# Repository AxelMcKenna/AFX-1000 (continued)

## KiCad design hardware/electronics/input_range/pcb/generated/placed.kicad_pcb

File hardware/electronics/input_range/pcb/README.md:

# E10 input-range PCB candidate

This separate **54 × 36 × 1.6 mm, six-layer candidate** implements the unchanged 28-part E10 schematic. Four Ø2.4 mm M2 holes have all-layer copper/via keepouts with 3.7 mm radius. It does not replace the existing A11 `audio_carrier`, which belongs to the output-stage board. This candidate has no assigned housing datum, component-height allocation or physical fit qualification.

The checked copper has **371 segments, 25 conventional through vias, zero native all-severity/all-track DRC or schematic-parity violations, and zero open connections** in KiCad 10.0.7. Native connectivity closure is an engineering milestone, not a fabrication release or measured preamplifier performance.

## Reproduce

```sh
python3 -m hardware.electronics.input_range.pcb.generate --reviewed --kicad-cli /path/to/kicad-cli
python3 -m hardware.electronics.input_range.pcb.check --kicad-cli /path/to/kicad-cli
python3 -m unittest discover -s tests/tooling -p test_input_range_pcb.py -v
```

`reviewed-copper.json` replays the checked copper only after the complete freshly generated placement matches its recorded hash. `generate --route` instead makes a new conservative routing attempt using the shared E25 routing primitives with board-specific rectangular bounds, clearances, drill exclusions and mounting keepouts. Every generation invalidates the existing verification record. A new attempt must pass the independent checker before use.

The preserved placement-only board is `generated/placed.kicad_pcb`; it has 50 connections before routing. Parent circuit values, all component pins, relay contacts, supply polarity, selected footprint names, faces/poses and mounts are independently checked against a fresh native schematic export and E10's authored circuit contract. The checker reports real native opens rather than trusting the route recipe or search-success flags. The six local feedback/output-to-feedback branches also have independent actual F.Cu graph checks: at least 0.25 mm width and a 12 mm construction limit. Those are layout rules, not a stability or bandwidth guarantee.

## Wiring boundary

J1 is `PROC_IN_L / AGND / PROC_IN_R`; J2 is `PRE_OUT_L / AGND / PRE_OUT_R`. J3 requires protected `P12 / AGND / N12`. J4 retains the parent's local `5V / GAIN_LOW` coil interface. The system harness explicitly connects that local `5V` to **protected `5V_DIG`**, never analog `V5_REG` or an unprotected `_SRC` rail. See the [system interconnect review](../../../wiring/SYSTEM.md).

## Remaining qualification

This exploratory routing uses six layers but **does not implement an uninterrupted analog ground plane**. Quiet returns, coil-current segregation, reference planes, amplifier bypass loops, input guards/capacitance, crosstalk, gain/calibration, stability, noise, distortion and overload/partial-power behavior need design review and measurement. Zero DRC does not establish any of them.

Component values and library footprints are inherited interface candidates. Exact passive/header part numbers, effective capacitance, purchased relay/amplifier package tolerances, copper stackup, soldering/stencil details, fasteners, strain relief and actual lead/body heights remain unqualified. The model deliberately leaves `MPN` empty instead of turning a generic resistor value into a purported purchase part number.

`generated/verification.json` fingerprints the current sources, actual PCB, native records and reused helpers. It keeps physical/audio/assembly and build-ready flags false. No board was ordered, powered, placed into the housing or measured in this work.

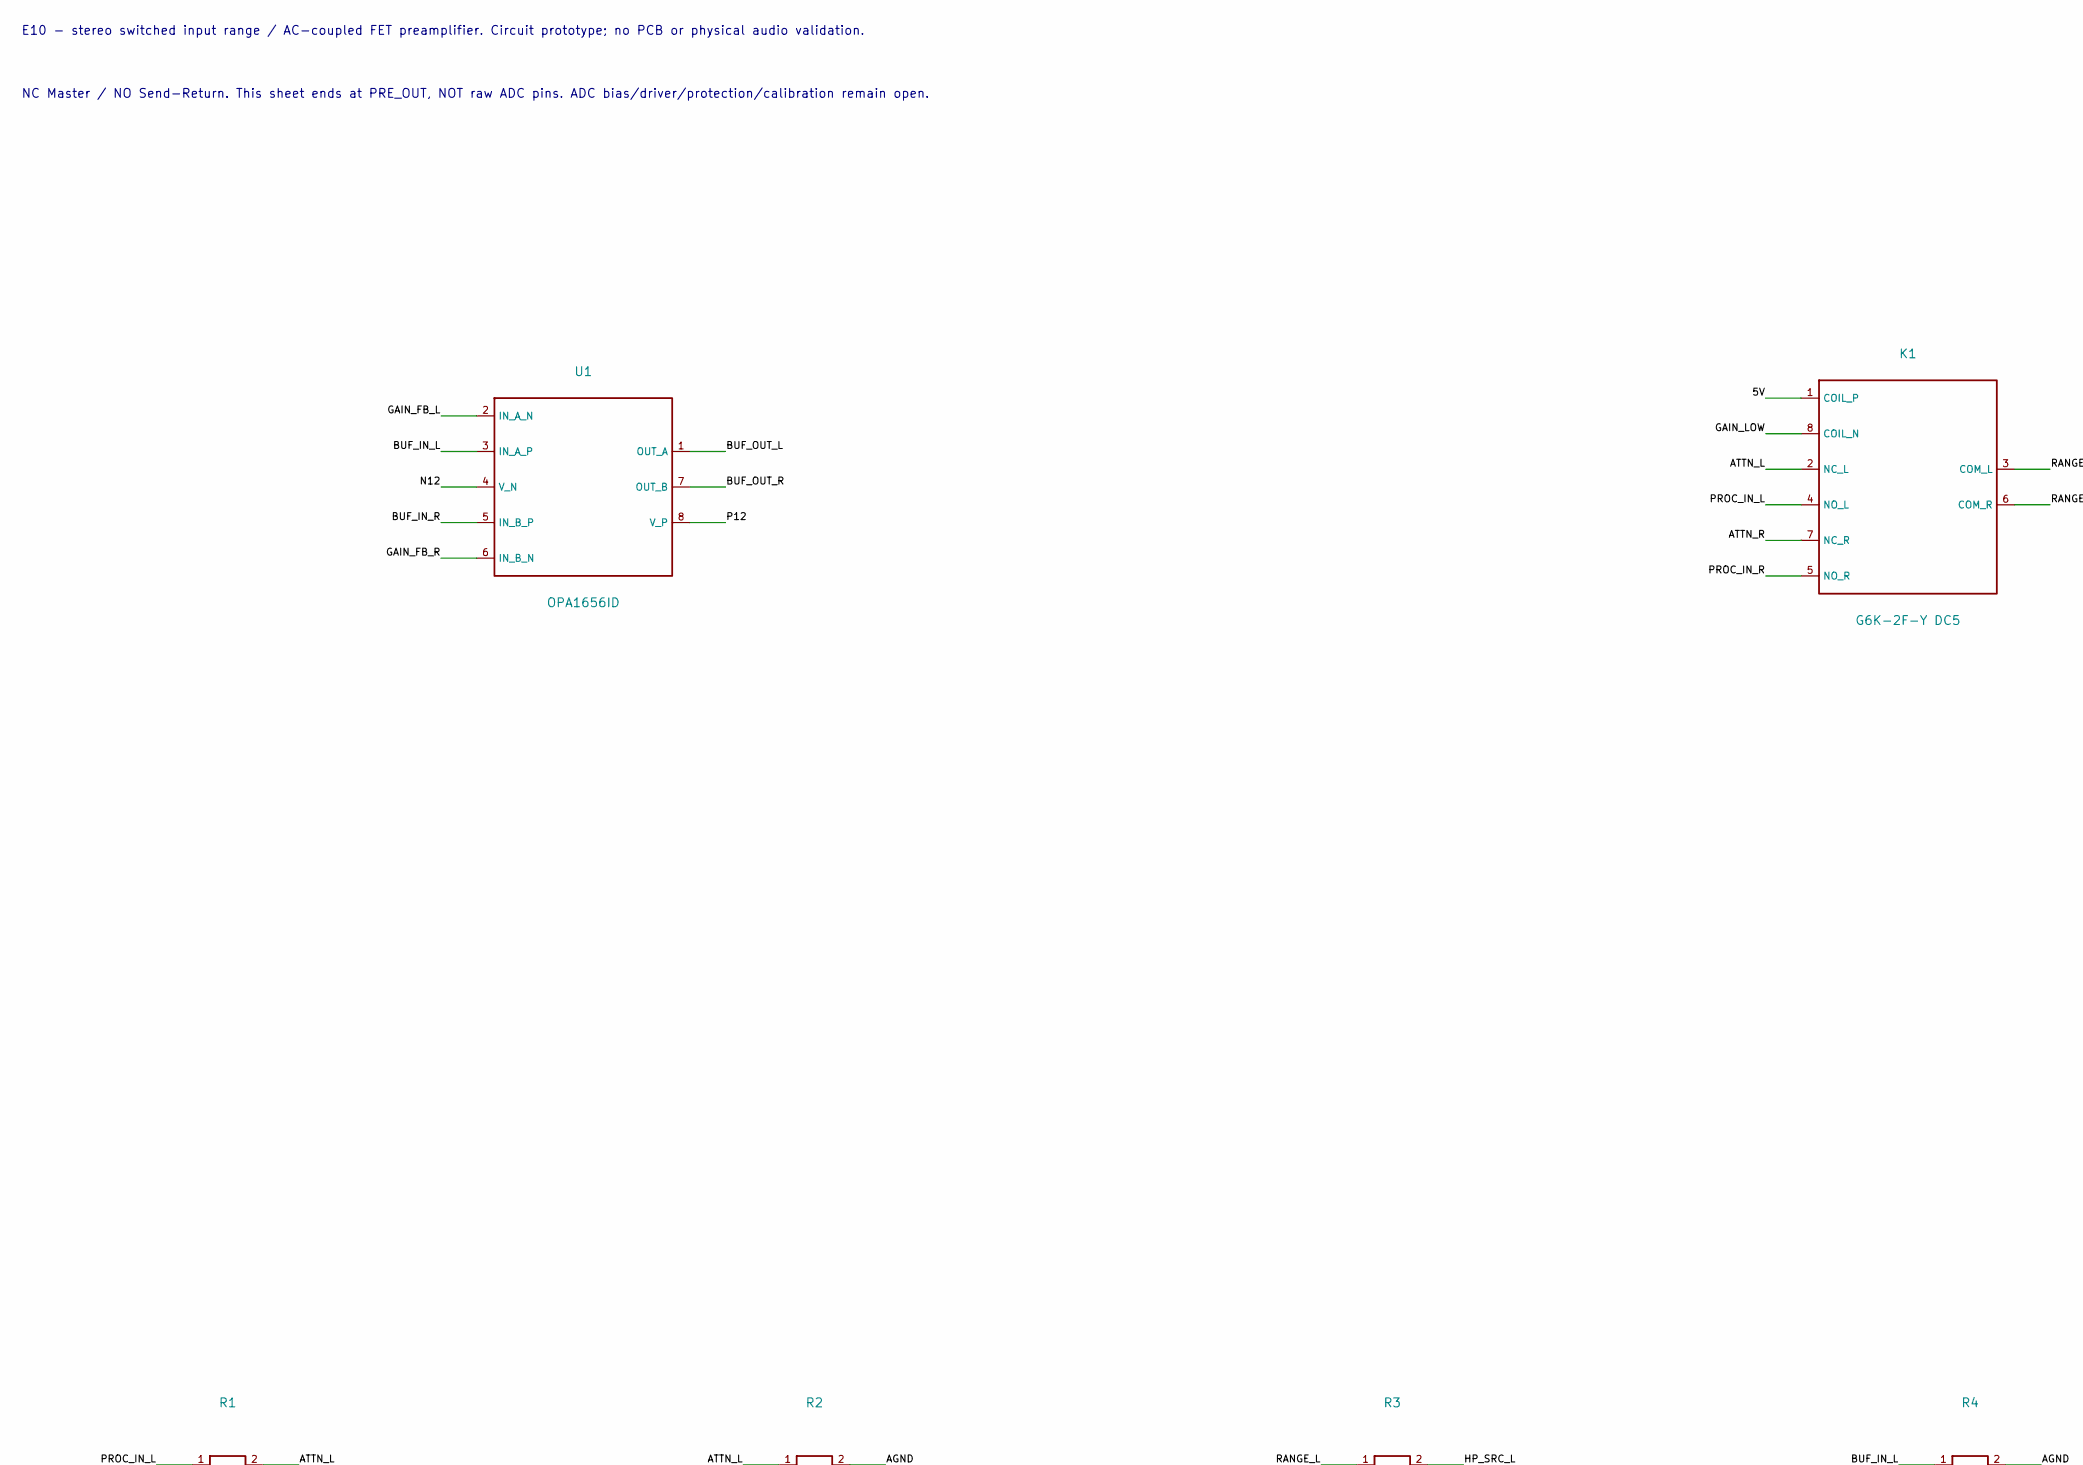
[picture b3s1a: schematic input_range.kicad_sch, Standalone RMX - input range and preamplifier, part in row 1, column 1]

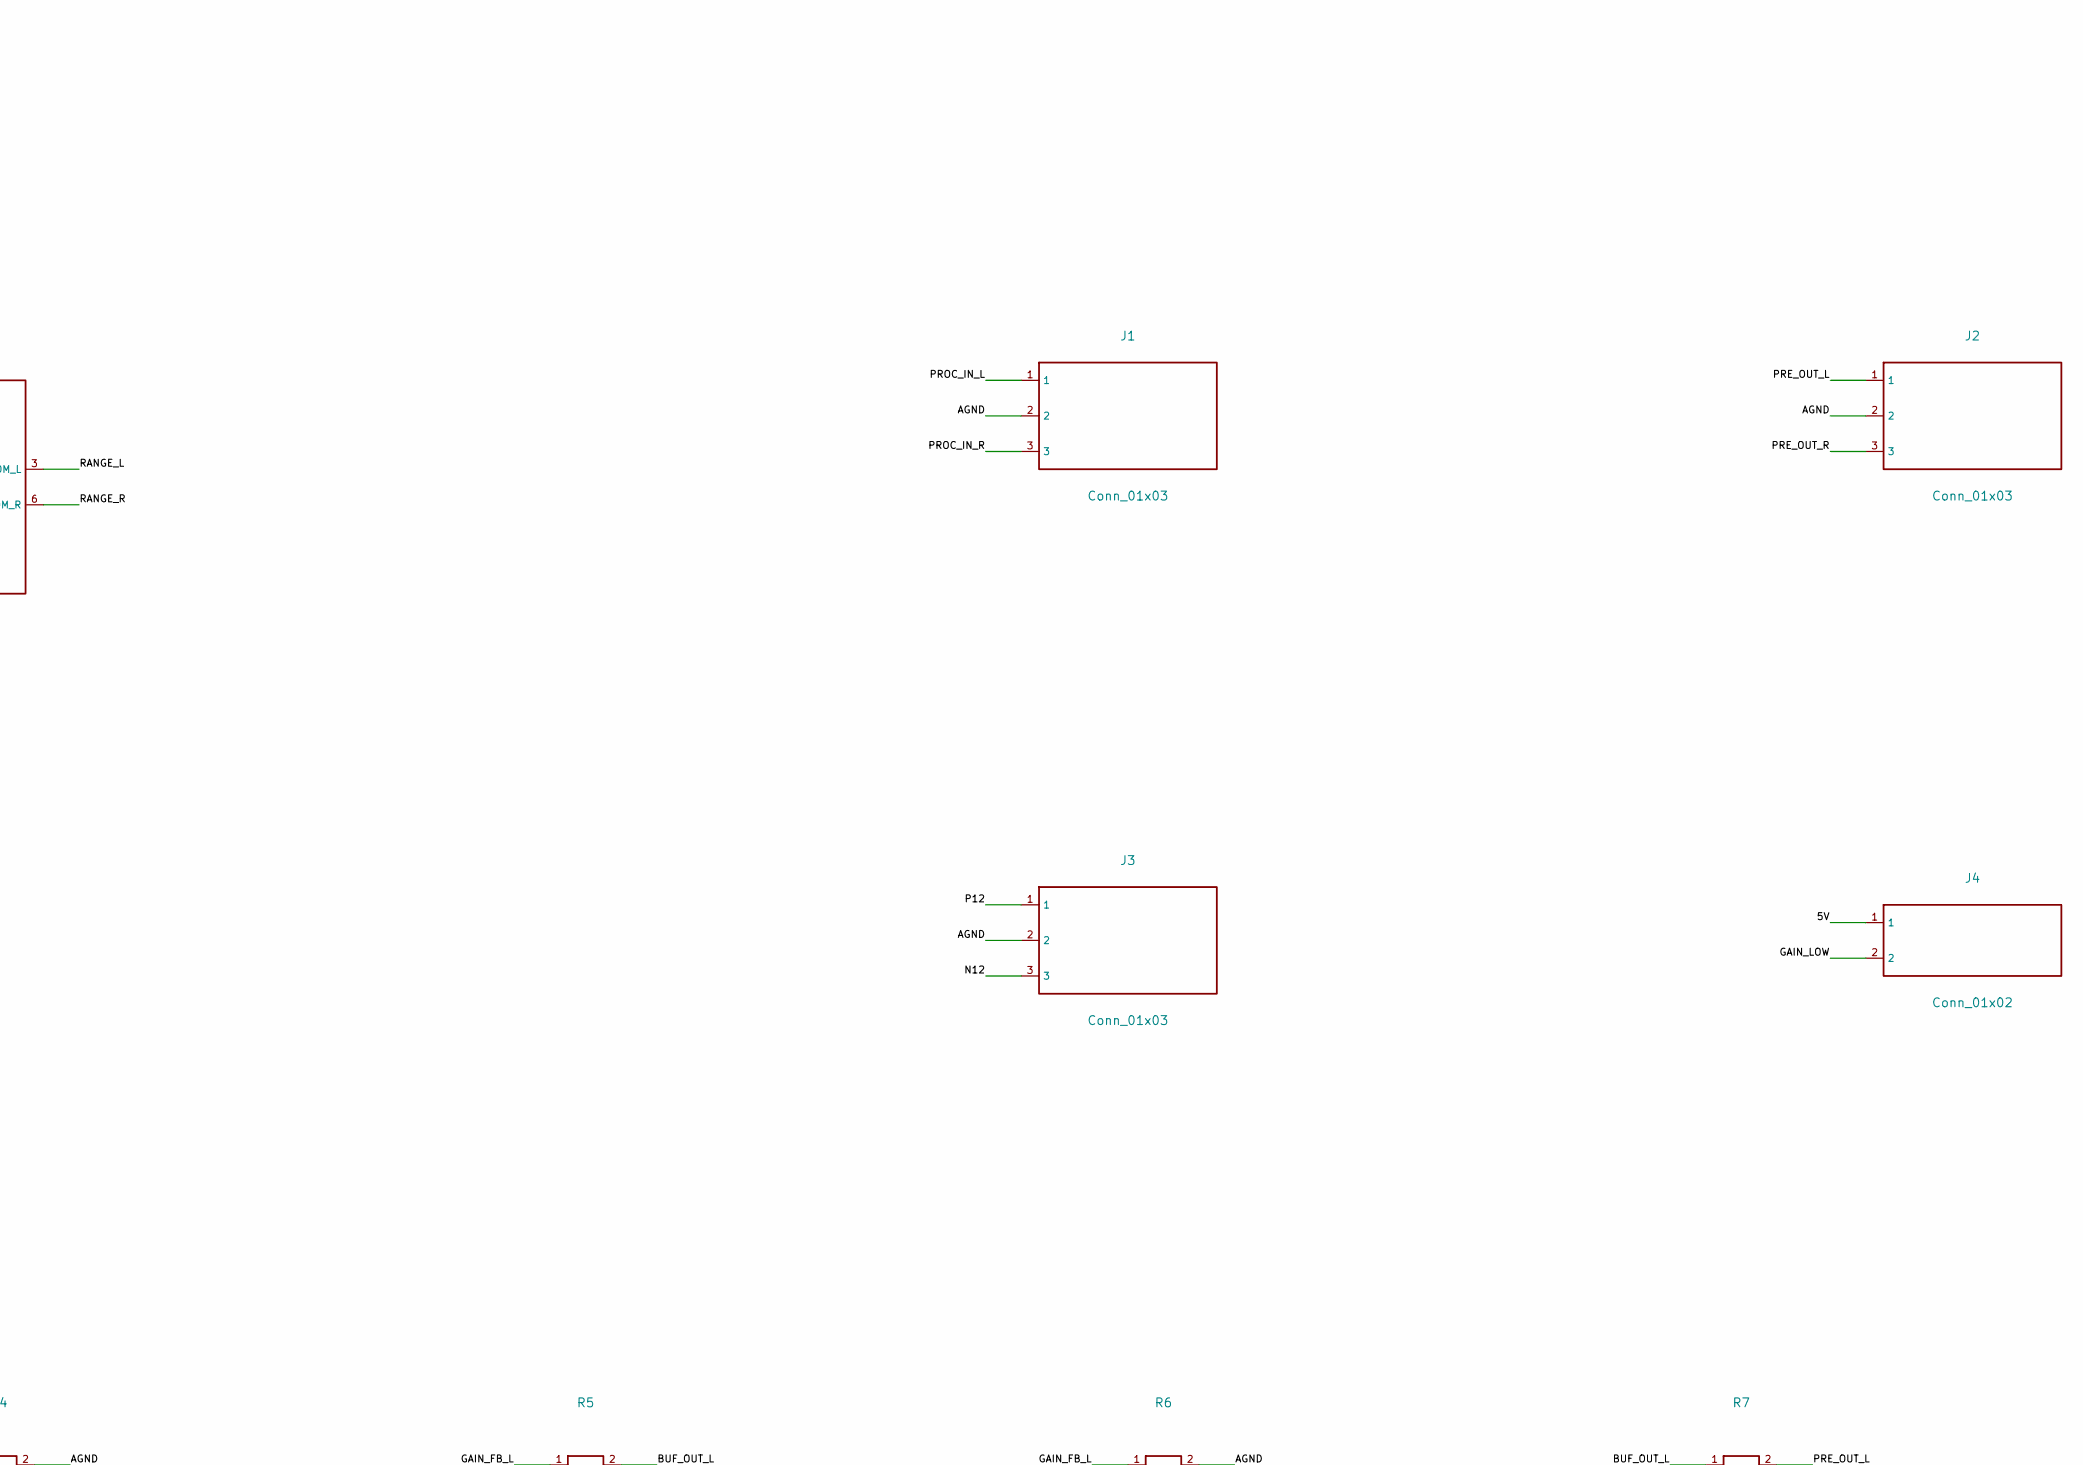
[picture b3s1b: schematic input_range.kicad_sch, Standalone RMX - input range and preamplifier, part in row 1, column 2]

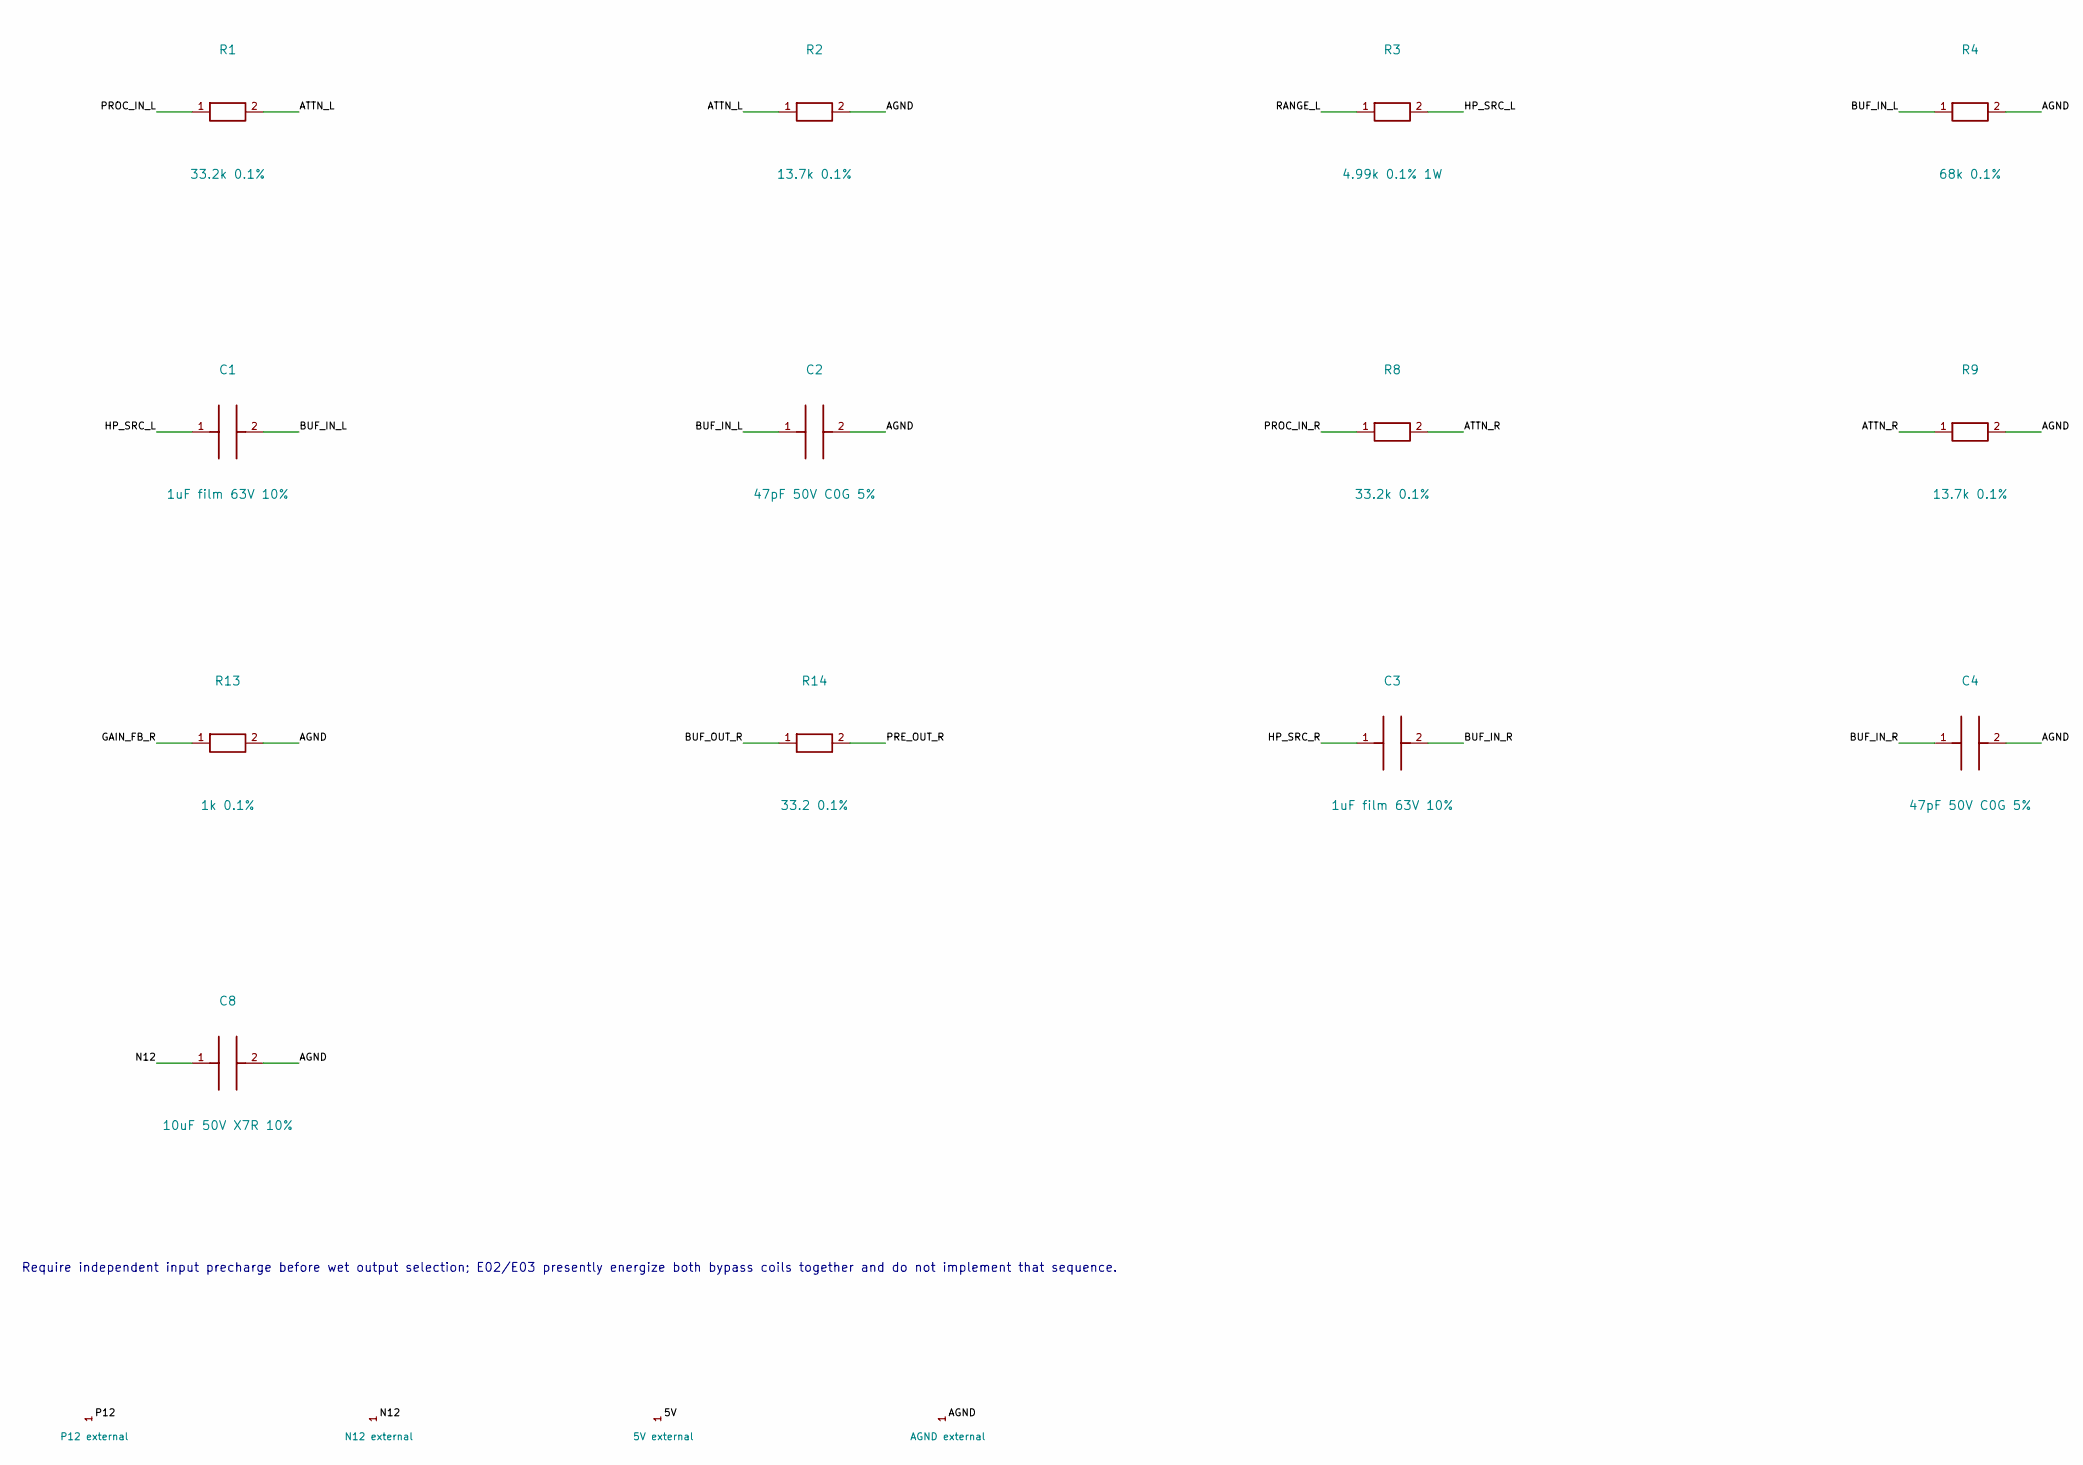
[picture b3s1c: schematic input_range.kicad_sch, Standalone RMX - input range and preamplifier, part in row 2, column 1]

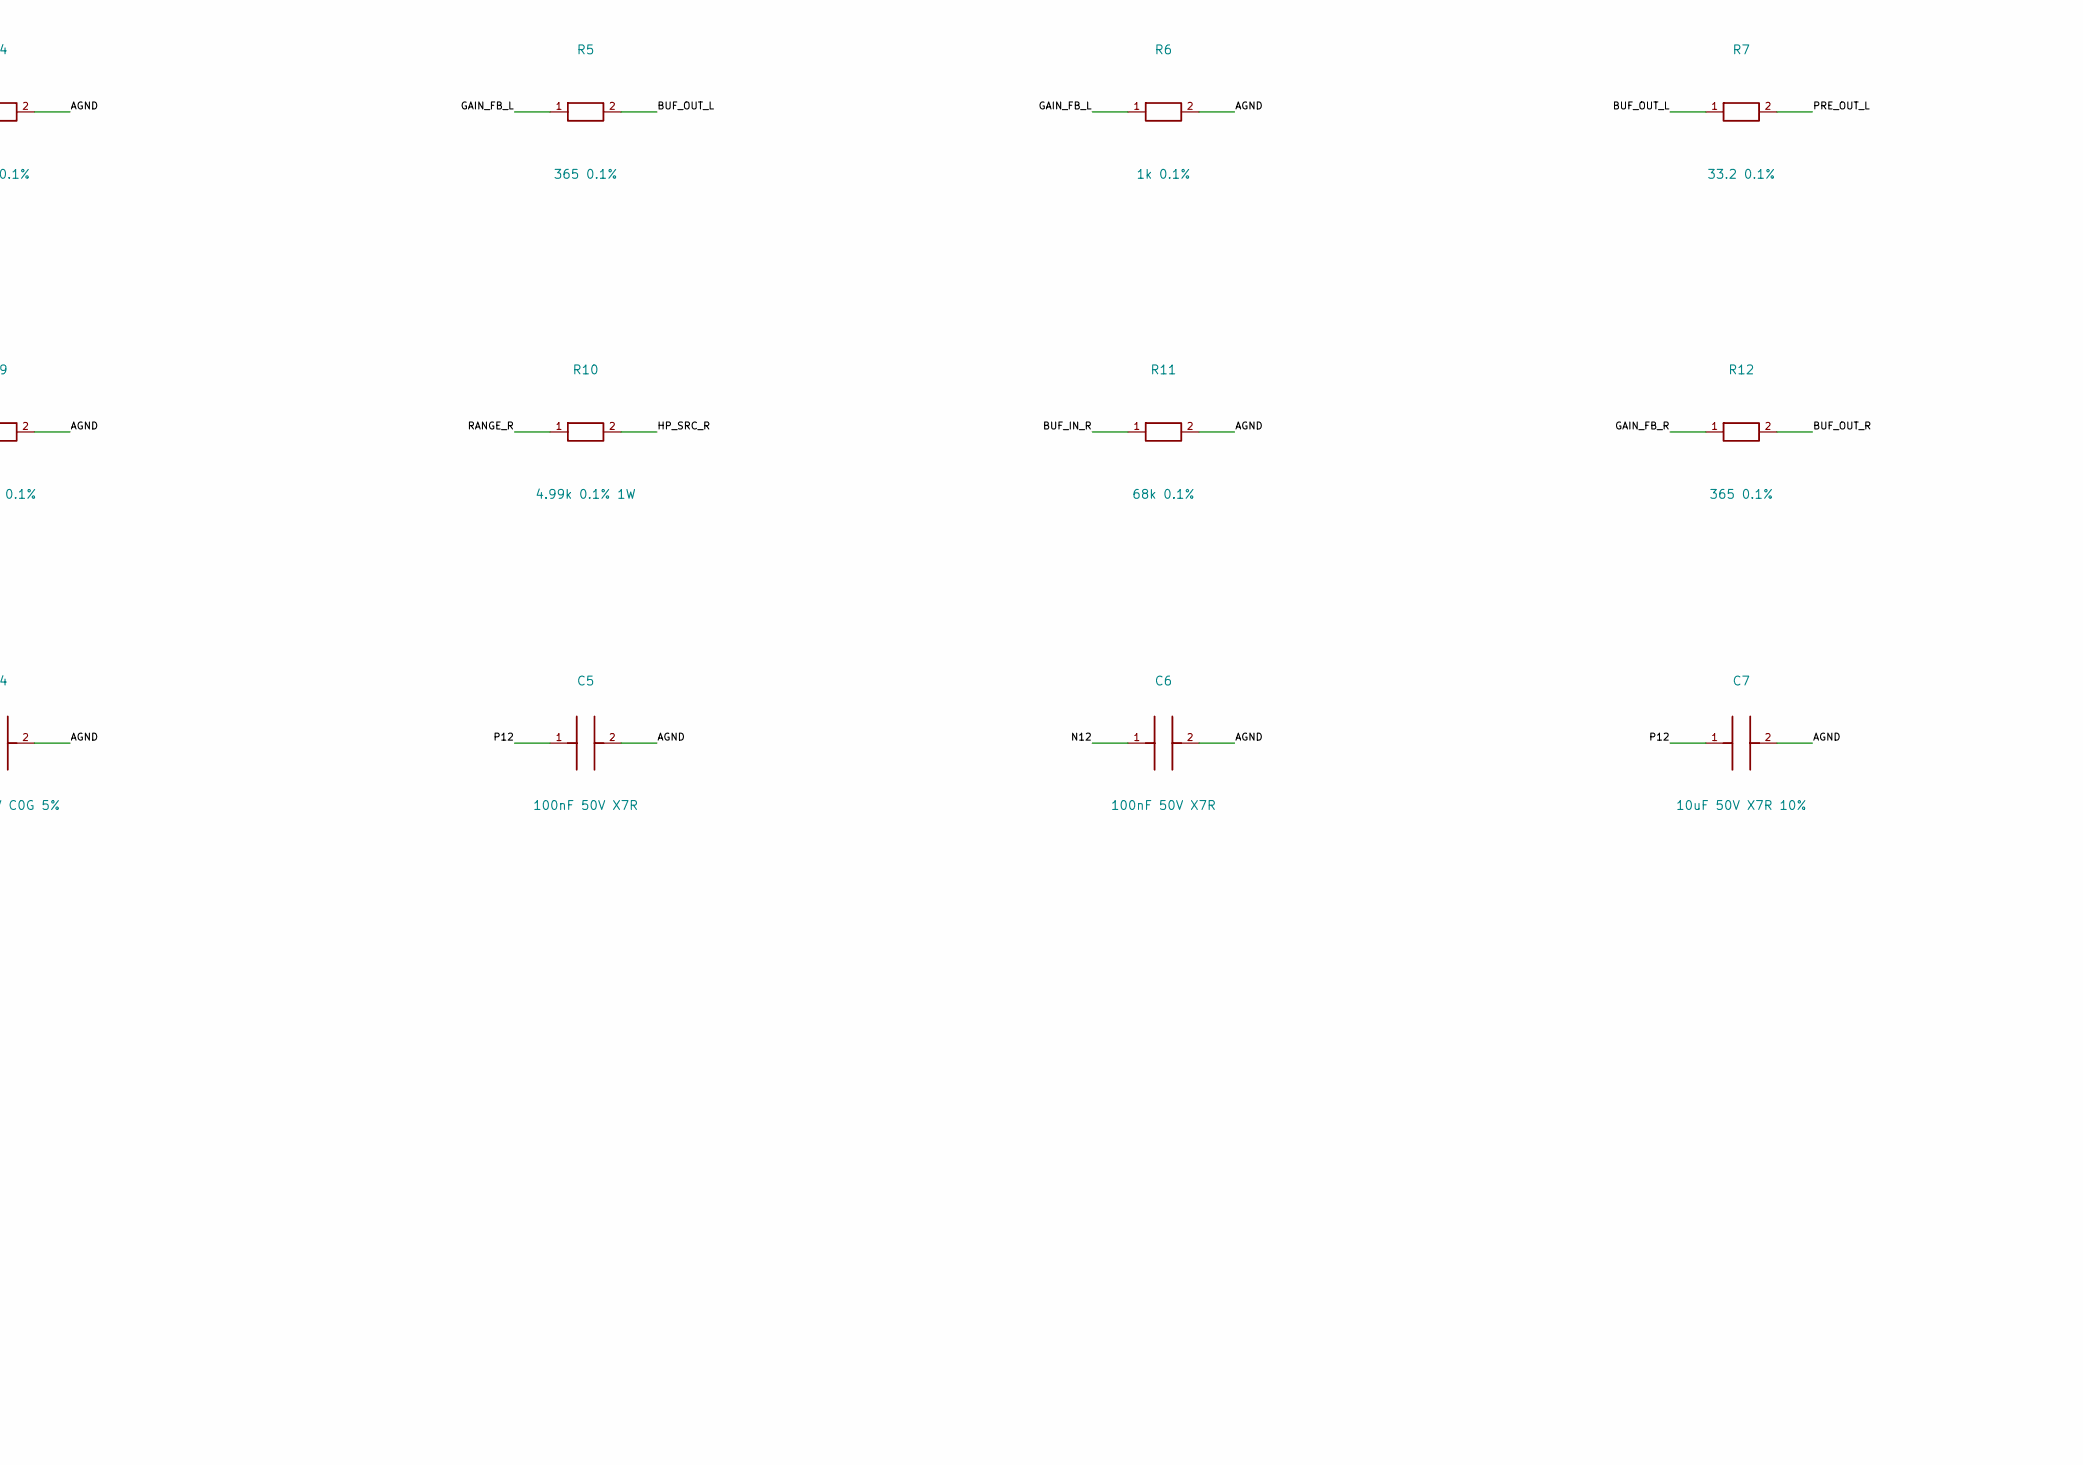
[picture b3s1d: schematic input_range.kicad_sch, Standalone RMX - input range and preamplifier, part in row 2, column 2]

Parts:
C1, C3: 1uF film 63V 10%; C_Rect_L7.2mm_W5.0mm_P5.00mm
C2, C4: 47pF 50V C0G 5%; C_0805_2012Metric
C5, C6: 100nF 50V X7R; C_0805_2012Metric
C7, C8: 10uF 50V X7R 10%; C_1210_3225Metric
J1, J2, J3: Conn_01x03; PinHeader_1x03_P2.54mm_Vertical
J4: Conn_01x02; PinHeader_1x02_P2.54mm_Vertical
K1: G6K-2F-Y DC5; Relay_DPDT_Omron_G6K-2F-Y
R1, R8: 33.2k 0.1%; R_0805_2012Metric
R2, R9: 13.7k 0.1%; R_0805_2012Metric
R3, R10: 4.99k 0.1% 1W; R_2512_6332Metric
R4, R11: 68k 0.1%; R_0805_2012Metric
R5, R12: 365 0.1%; R_0805_2012Metric
R6, R13: 1k 0.1%; R_0805_2012Metric
R7, R14: 33.2 0.1%; R_0805_2012Metric
U1: OPA1656ID; SOIC-8_3.9x4.9mm_P1.27mm

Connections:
/5V: J4.1, K1.1 (COIL_P)
/AGND: C2.2, C4.2, C5.2, C6.2, C7.2, C8.2, J1.2, J2.2, J3.2, R2.2, R4.2, R6.2, R9.2, R11.2, R13.2
/ATTN_L: K1.2 (NC_L), R1.2, R2.1
/ATTN_R: K1.7 (NC_R), R8.2, R9.1
/BUF_IN_L: C1.2, C2.1, R4.1, U1.3 (IN_A_P)
/BUF_IN_R: C3.2, C4.1, R11.1, U1.5 (IN_B_P)
/BUF_OUT_L: R5.2, R7.1, U1.1 (OUT_A)
/BUF_OUT_R: R12.2, R14.1, U1.7 (OUT_B)
/GAIN_FB_L: R5.1, R6.1, U1.2 (IN_A_N)
/GAIN_FB_R: R12.1, R13.1, U1.6 (IN_B_N)
/GAIN_LOW: J4.2, K1.8 (COIL_N)
/HP_SRC_L: C1.1, R3.2
/HP_SRC_R: C3.1, R10.2
/N12: C6.1, C8.1, J3.3, U1.4 (V_N)
/P12: C5.1, C7.1, J3.1, U1.8 (V_P)
/PRE_OUT_L: J2.1, R7.2
/PRE_OUT_R: J2.3, R14.2
/PROC_IN_L: J1.1, K1.4 (NO_L), R1.1
/PROC_IN_R: J1.3, K1.5 (NO_R), R8.1
/RANGE_L: K1.3 (COM_L), R3.1
/RANGE_R: K1.6 (COM_R), R10.1

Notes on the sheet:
E10 - stereo switched input range / AC-coupled FET preamplifier. Circuit prototype; no PCB or physical audio validation.
NC Master / NO Send-Return. This sheet ends at PRE_OUT, NOT raw ADC pins. ADC bias/driver/protection/calibration remain open.
Require independent input precharge before wet output selection; E02/E03 presently energize both bypass coils together and do not implement that sequence.

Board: 6 copper layers, 32 parts (1 on the bottom side), 21 nets, no tracks yet.

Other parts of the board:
H1, H2, H3, H4: M2_CLEARANCE; M2_Clearance

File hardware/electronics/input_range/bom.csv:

Reference,Part_or_value,Footprint_candidate,Datasheet,Design_note
U1,OPA1656ID,Package_SO:SOIC-8_3.9x4.9mm_P1.27mm,https://www.ti.com/lit/ds/symlink/opa1656.pdf,"Dual FET input preamplifier, nominal gain1.365. +/-12V only. Gain resistor remains subject to full ADC-scale calibration."
K1,G6K-2F-Y DC5,Relay_SMD:Relay_DPDT_Omron_G6K-2F-Y,https://omronfs.omron.com/en_US/ecb/products/pdf/en-g6k.pdf,"Released NC=Master attenuated; energized NO=Send/Return. Second gain coil on E02 driver, independent of wet/dry selection."
J1,Conn_01x03,Connector_PinHeader_2.54mm:PinHeader_1x03_P2.54mm_Vertical,,E03 processing input J3.1..3. Its input-isolation coil currently shares wet/dry enable; independent precharge sequencing is not implemented.
J2,Conn_01x03,Connector_PinHeader_2.54mm:PinHeader_1x03_P2.54mm_Vertical,,"Single-ended preamplifier output to future ADC driver, NOT E09 raw ADC input. Analysis assumes load>=100kOhm; scale/bias/protection unresolved."
J3,Conn_01x03,Connector_PinHeader_2.54mm:PinHeader_1x03_P2.54mm_Vertical,,Qualified regulated +/-12V; rail generation/monitoring external.
J4,Conn_01x02,Connector_PinHeader_2.54mm:PinHeader_1x02_P2.54mm_Vertical,,Same pair/order as E02 J5 and E05 J3; second of two proposed gain coils.
R1,33.2k 0.1%,Resistor_SMD:R_0805_2012Metric,,Master divider upper; remains connected in both ranges.
R2,13.7k 0.1%,Resistor_SMD:R_0805_2012Metric,,Master divider lower; includes the actual following bias network load.
R3,4.99k 0.1% 1W,Resistor_SMD:R_2512_6332Metric,,Limits a hypothetical48V input/capacitor step to<10mA; exact resistor/pulse/temperature qualification open.
R4,68k 0.1%,Resistor_SMD:R_0805_2012Metric,,FET input DC return; hot bias/leakage allocation and input precharge interval required.
R5,365 0.1%,Resistor_SMD:R_0805_2012Metric,,Nominal gain resistor. Final value requires complete ADC input-scale measurements.
R6,1k 0.1%,Resistor_SMD:R_0805_2012Metric,,Noninverting gain ground leg.
R7,33.2 0.1%,Resistor_SMD:R_0805_2012Metric,,Output isolation; future ADC driver must present>=100kOhm in-band.
C1,1uF film 63V 10%,Capacitor_THT:C_Rect_L7.2mm_W5.0mm_P5.00mm,https://wima.de/wp-content/uploads/media/e_WIMA_MKS_2.pdf,"WIMA MKS2C041001F00KSSD candidate: nominal7.2x5x10mm body,5mm pitch. Nonpolar; leakage/temperature/fit not measured."
C2,47pF 50V C0G 5%,Capacitor_SMD:C_0805_2012Metric,,RF shunt; not a rated surge/ESD suppressor.
R8,33.2k 0.1%,Resistor_SMD:R_0805_2012Metric,,Master divider upper; remains connected in both ranges.
R9,13.7k 0.1%,Resistor_SMD:R_0805_2012Metric,,Master divider lower; includes the actual following bias network load.
R10,4.99k 0.1% 1W,Resistor_SMD:R_2512_6332Metric,,Limits a hypothetical48V input/capacitor step to<10mA; exact resistor/pulse/temperature qualification open.
R11,68k 0.1%,Resistor_SMD:R_0805_2012Metric,,FET input DC return; hot bias/leakage allocation and input precharge interval required.
R12,365 0.1%,Resistor_SMD:R_0805_2012Metric,,Nominal gain resistor. Final value requires complete ADC input-scale measurements.
R13,1k 0.1%,Resistor_SMD:R_0805_2012Metric,,Noninverting gain ground leg.
R14,33.2 0.1%,Resistor_SMD:R_0805_2012Metric,,Output isolation; future ADC driver must present>=100kOhm in-band.
C3,1uF film 63V 10%,Capacitor_THT:C_Rect_L7.2mm_W5.0mm_P5.00mm,https://wima.de/wp-content/uploads/media/e_WIMA_MKS_2.pdf,"WIMA MKS2C041001F00KSSD candidate: nominal7.2x5x10mm body,5mm pitch. Nonpolar; leakage/temperature/fit not measured."
C4,47pF 50V C0G 5%,Capacitor_SMD:C_0805_2012Metric,,RF shunt; not a rated surge/ESD suppressor.
C5,100nF 50V X7R,Capacitor_SMD:C_0805_2012Metric,,Local U1 supply bypass
C6,100nF 50V X7R,Capacitor_SMD:C_0805_2012Metric,,Local U1 supply bypass
C7,10uF 50V X7R 10%,Capacitor_SMD:C_1210_3225Metric,,"Require effective>=4.7uF on +/-12V; exact MPN, bias/temperature/ESR unqualified."
C8,10uF 50V X7R 10%,Capacitor_SMD:C_1210_3225Metric,,"Require effective>=4.7uF on +/-12V; exact MPN, bias/temperature/ESR unqualified."

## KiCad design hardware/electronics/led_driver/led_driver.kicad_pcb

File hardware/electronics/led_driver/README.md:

# E20 LED and BPM driver

E20 implements the 96-output feedback interface used by the standalone firmware:
four TLC5947DAPR constant-current drivers, a 3.3-to-5 V translator, and independent
3.3 V/5 V supervisors. It covers the driver core. The front-panel emitter boards,
display wiring, ring optics and production harnesses are unfinished.

The independent [verification record](generated/verification.json), when present,
states whether the native PCB is placed or routed. An explicitly requested
`--placed-only` result permits open connections and is not a routing approval.
The normal verifier requires zero native ERC, DRC, schematic-parity and open
connections, and a saved ground-plane fill. No physical qualification is claimed.

## Power and startup

The four TLC5947s use `5V_DIG`. Their 16.5 kΩ IREF resistors set approximately
2.98 mA per output by TI's nominal formula. The drivers' guaranteed accuracy and
ICC test conditions are at other reference currents; 2.98 mA is not an established
maximum. The provisional engineering allocation is 4 mA per sink, 90 mA ICC per
driver and 20 mA miscellaneous load: **764 mA total**, including the emitters.
That allocation requires physical verification at the selected IREF value.

U5 is an SN74LVC8T245PWR. VCCA and its input controls use `V3V3_IO` from the
processor; VCCB uses `5V_DIG`. DIR is held high. Four channels translate the
firmware's MOSI, clock, latch and BLANK signals. Four unused A inputs are grounded,
with the corresponding B outputs unconnected. Each active output has a 33 Ω
series resistor. Receiving BLANK is pulled high to keep the drivers off while
the translator is disabled; the other three receiving signals have pulldowns.

TPS3808G33/G50 supervisors monitor both domains. Their settled PG outputs drive
two series NMOS switches: both must be high to pull translator `/OE` low. Missing
or unsettled power leaves `/OE` pulled high. The independent checker follows the
actual MOSFET body-diode directions in eight ideal PG/BLANK combinations. This
does not establish real brownout, back-power or restore-frame behavior.

Firmware holds BLANK high at startup and on SPI failure, shifts each new frame
into the separate shift registers, and explicitly provides 1 µs guards
before/after the latch pulse and before clearing BLANK. Host wire tests model
four cascaded 288-bit shift registers and walk all 1,152 PWM bits. Physical SPI
edge timing, cable integrity and recovery still need measurement.

## Connections

| Connector | Assignment |
| --- | --- |
| J1, 2×4, 1.27 mm | 1 AGND; 2 5V_DIG; 3 V3V3_IO; 4 LED_MOSI; 5 LED_SCK; 6 LED_XLAT; 7 LED_BLANK; 8 AGND |
| J2, 2×13, 2.54 mm | Pins 1–12: LED_23…12; 13–24: LED_47…36; 25/26: common anode 5V_DIG |
| J3, 2×13, 2.54 mm | Pins 1–12: LED_00…11; 13–24: LED_24…35; 25/26: common anode 5V_DIG |
| J4, 2×13, 2.54 mm | Pins 1–12: LED_71…60; 13–24: LED_95…84; 25/26: common anode 5V_DIG |
| J5, 2×13, 2.54 mm | Pins 1–12: LED_48…59; 13–24: LED_72…83; 25/26: common anode 5V_DIG |

J1 matches E19 J11 by pin number. The two connectors have different pitches and
require a correctly mapped adapter harness. The [channel map](generated/channel-map.csv)
lists every logical lamp, meter, display segment and RGB output by IC and pin.
Output order follows each driver's physical banks; it does not change firmware
channel order. Emitter cathodes connect to driver outputs, with common anodes at
5 V. Exact emitters, brightness, colour balance and forward-voltage headroom are
unqualified.

## PCB and mechanical proposal

The six-layer board is 91×27×1.6 mm, proposed at housing coordinates
(197,77,6.5). Its M2 clearance holes are (3,7), (87,7), (3,22), (87,22), relative
to the PCB corner. Routing uses 0.15 mm minimum traces/clearance, 0.6/0.3 mm
through vias, In1/In4 ground planes and four mounting copper keepouts across all
six layers. The extra signal layer retains routing space in this small footprint
at increased board cost. The input,
bulk capacitor and common-anode headers have 0.8 mm power routes; IC supply
branches use 0.25 mm. Copper thickness, voltage drop, current rise and thermal
behavior require a final stackup and qualification.

The local TLC5947 footprint follows TI's DAP0032C drawing: 32 signal lands,
grounded EP33 and four paste windows. Thermal vias sit outside the paste/mask
opening. A local footprint audit checks those dimensions; stencil fabrication,
package variant, soldering and actual thermal resistance remain unqualified.
The placement packet reserves top connector/harness height of at most 11 mm,
bottom bulk-capacitor height of at most 3 mm, and trimmed/soldered header tails
of at most 3 mm. These are assembly limits, not selected production parts.

## Integration limits

The [power reconciliation](generated/power-reconciliation.json) refreshes and
fingerprints the E21 adaptations of E14/E16/E17. The 764 mA LED allocation is
counted once in the 1.574 A system ledger, against 1.8 A provision. E16's slower
input ramp and higher current setting retain about 101 mA under a conditional
2.773 A combined steady/input/digital-capacitor ramp. E17's two parallel devices
on each digital leg retain a 4.9028–5.0992 V protected-star range under the
declared hot-resistance and ripple allocations.

These passing screens assume the protected digital bulk is connected before
the source ramps. Other rails' charging, late switch closure, actual 6.5 mF
capacitance bound, large-capacitor loop stability, increased gate charge, thermal
limits, LED ICC at 16.5 kΩ IREF and distribution/contact drops remain unqualified.
The very small 5 V margins require measurement. Full-unit power closure and
assembly release remain open. The immutable A06/E20 review ZIP retains the
earlier failed 1.2 A, 2.693 A startup and 4.8982 V screens as historical evidence.

## Reproduce

From the repository root, with Python, NumPy and native KiCad 10:

```sh
python3 -m hardware.electronics.led_driver.generate
python3 -m hardware.electronics.led_driver.place --kicad-cli /path/to/kicad-cli
python3 -m hardware.electronics.led_driver.route
python3 -m hardware.electronics.led_driver.cleanup --kicad-cli /path/to/kicad-cli
python3 -m hardware.electronics.led_driver.verify --kicad-cli /path/to/kicad-cli
```

Refresh upstream verifiers in order `power_supply`, `input_protection`,
`rail_disconnect` before E20 verification if their source fingerprints differ.
`route --fanout-only` and failed-routing intermediates go to the ignored
`build/artifacts/research/e20-routing/` directory. Routing and cleanup are
generation aids; independent native verification is
required. Manufacturer links and downloaded-source hashes are in
[dependencies.json](dependencies.json).

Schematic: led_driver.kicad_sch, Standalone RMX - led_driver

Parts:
C1, C3, C5, C7, C9, C10, C11, C12: 100nF 16V X7R; C_0603_1608Metric
C2, C4, C6, C8, C14: 4.7uF 16V X7R; C_0805_2012Metric
C13: 22uF 25V X7R; C_1210_3225Metric
J1: Header8; PinHeader_2x04_P1.27mm_Vertical
J2, J3, J4, J5: Header26; PinHeader_2x13_P2.54mm_Vertical
Q1, Q2: AO3400A; SOT-23
R1, R2, R3, R4: 16.5k 1%; R_0603_1608Metric
R5: 47k 1%; R_0603_1608Metric
R6, R7, R10, R11: 10k 1%; R_0603_1608Metric
R8, R9, R12, R13, R14, R19, R20, R21: 100k 1%; R_0603_1608Metric
R15, R16, R17, R18: 33R 1%; R_0603_1608Metric
U1, U2, U3, U4: TLC5947DAPR; TLC5947_DAP0032C
U5: SN74LVC8T245PWR; TSSOP-24_4.4x7.8mm_P0.65mm
U6: TPS3808G33DBVR; SOT-23-6
U7: TPS3808G50DBVR; SOT-23-6

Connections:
/5V_DIG: C1.1, C2.1, C3.1, C4.1, C5.1, C6.1, C7.1, C8.1, C10.1, C12.1, C13.1, C14.1, J1.2, J2.25, J2.26, J3.25, J3.26, J4.25, J4.26, J5.25, J5.26, R7.2, R11.2, U1.32 (VCC), U2.32 (VCC), U3.32 (VCC), U4.32 (VCC), U5.23 (VCCB), U5.24 (VCCB), U7.3 (MR_N), U7.5 (SENSE), U7.6 (VDD)
/AGND: C1.2, C2.2, C3.2, C4.2, C5.2, C6.2, C7.2, C8.2, C9.2, C10.2, C11.2, C12.2, C13.2, C14.2, J1.1, J1.8, Q2.2 (S), R1.2, R2.2, R3.2, R4.2, R8.2, R9.2, R12.2, R13.2, R14.2, R19.2, R20.2, R21.2, U1.1 (GND), U1.33 (EP), U2.1 (GND), U2.33 (EP), U3.1 (GND), U3.33 (EP), U4.1 (GND), U4.33 (EP), U5.7 (A5), U5.8 (A6), U5.9 (A7), U5.10 (A8), U5.11 (GND), U5.12 (GND), U5.13 (GND), U6.2 (GND), U7.2 (GND)
/BLANK_5V: R11.1, R18.2, U1.2 (BLANK), U2.2 (BLANK), U3.2 (BLANK), U4.2 (BLANK)
/BLANK_5V_SRC: R18.1, U5.18 (B4)
/CLOCK_5V: R13.1, R16.2, U1.3 (SCLK), U2.3 (SCLK), U3.3 (SCLK), U4.3 (SCLK)
/CLOCK_5V_SRC: R16.1, U5.20 (B2)
/DATA_5V: R12.1, R15.2, U1.4 (SIN)
/DATA_5V_SRC: R15.1, U5.21 (B1)
/ENABLE_MID: Q1.2 (S), Q2.3 (D)
/IREF_0: R1.1, U1.31 (IREF)
/IREF_1: R2.1, U2.31 (IREF)
/IREF_2: R3.1, U3.31 (IREF)
/IREF_3: R4.1, U4.31 (IREF)
/LATCH_5V: R14.1, R17.2, U1.30 (XLAT), U2.30 (XLAT), U3.30 (XLAT), U4.30 (XLAT)
/LATCH_5V_SRC: R17.1, U5.19 (B3)
/LED_00: J3.1, U1.5 (OUT0)
/LED_01: J3.2, U1.6 (OUT1)
/LED_02: J3.3, U1.7 (OUT2)
/LED_03: J3.4, U1.8 (OUT3)
/LED_04: J3.5, U1.9 (OUT4)
/LED_05: J3.6, U1.10 (OUT5)
/LED_06: J3.7, U1.11 (OUT6)
/LED_07: J3.8, U1.12 (OUT7)
/LED_08: J3.9, U1.13 (OUT8)
/LED_09: J3.10, U1.14 (OUT9)
/LED_10: J3.11, U1.15 (OUT10)
/LED_11: J3.12, U1.16 (OUT11)
/LED_12: J2.12, U1.17 (OUT12)
/LED_13: J2.11, U1.18 (OUT13)
/LED_14: J2.10, U1.19 (OUT14)
/LED_15: J2.9, U1.20 (OUT15)
/LED_16: J2.8, U1.21 (OUT16)
/LED_17: J2.7, U1.22 (OUT17)
/LED_18: J2.6, U1.23 (OUT18)
/LED_19: J2.5, U1.24 (OUT19)
/LED_20: J2.4, U1.25 (OUT20)
/LED_21: J2.3, U1.26 (OUT21)
/LED_22: J2.2, U1.27 (OUT22)
/LED_23: J2.1, U1.28 (OUT23)
/LED_24: J3.13, U2.5 (OUT0)
/LED_25: J3.14, U2.6 (OUT1)
/LED_26: J3.15, U2.7 (OUT2)
/LED_27: J3.16, U2.8 (OUT3)
/LED_28: J3.17, U2.9 (OUT4)
/LED_29: J3.18, U2.10 (OUT5)
/LED_30: J3.19, U2.11 (OUT6)
/LED_31: J3.20, U2.12 (OUT7)
/LED_32: J3.21, U2.13 (OUT8)
/LED_33: J3.22, U2.14 (OUT9)
/LED_34: J3.23, U2.15 (OUT10)
/LED_35: J3.24, U2.16 (OUT11)
/LED_36: J2.24, U2.17 (OUT12)
/LED_37: J2.23, U2.18 (OUT13)
/LED_38: J2.22, U2.19 (OUT14)
/LED_39: J2.21, U2.20 (OUT15)
/LED_40: J2.20, U2.21 (OUT16)
/LED_41: J2.19, U2.22 (OUT17)
/LED_42: J2.18, U2.23 (OUT18)
/LED_43: J2.17, U2.24 (OUT19)
/LED_44: J2.16, U2.25 (OUT20)
/LED_45: J2.15, U2.26 (OUT21)
/LED_46: J2.14, U2.27 (OUT22)
/LED_47: J2.13, U2.28 (OUT23)
/LED_48: J5.1, U3.5 (OUT0)
/LED_49: J5.2, U3.6 (OUT1)
/LED_50: J5.3, U3.7 (OUT2)
/LED_51: J5.4, U3.8 (OUT3)
/LED_52: J5.5, U3.9 (OUT4)
/LED_53: J5.6, U3.10 (OUT5)
/LED_54: J5.7, U3.11 (OUT6)
/LED_55: J5.8, U3.12 (OUT7)
/LED_56: J5.9, U3.13 (OUT8)
/LED_57: J5.10, U3.14 (OUT9)
/LED_58: J5.11, U3.15 (OUT10)
/LED_59: J5.12, U3.16 (OUT11)
/LED_60: J4.12, U3.17 (OUT12)
/LED_61: J4.11, U3.18 (OUT13)
/LED_62: J4.10, U3.19 (OUT14)
/LED_63: J4.9, U3.20 (OUT15)
/LED_64: J4.8, U3.21 (OUT16)
/LED_65: J4.7, U3.22 (OUT17)
/LED_66: J4.6, U3.23 (OUT18)
/LED_67: J4.5, U3.24 (OUT19)
/LED_68: J4.4, U3.25 (OUT20)
/LED_69: J4.3, U3.26 (OUT21)
/LED_70: J4.2, U3.27 (OUT22)
/LED_71: J4.1, U3.28 (OUT23)
/LED_72: J5.13, U4.5 (OUT0)
/LED_73: J5.14, U4.6 (OUT1)
/LED_74: J5.15, U4.7 (OUT2)
/LED_75: J5.16, U4.8 (OUT3)
/LED_76: J5.17, U4.9 (OUT4)
/LED_77: J5.18, U4.10 (OUT5)
/LED_78: J5.19, U4.11 (OUT6)
/LED_79: J5.20, U4.12 (OUT7)
/LED_80: J5.21, U4.13 (OUT8)
/LED_81: J5.22, U4.14 (OUT9)
/LED_82: J5.23, U4.15 (OUT10)
/LED_83: J5.24, U4.16 (OUT11)
/LED_84: J4.24, U4.17 (OUT12)
/LED_85: J4.23, U4.18 (OUT13)
/LED_86: J4.22, U4.19 (OUT14)
/LED_87: J4.21, U4.20 (OUT15)
/LED_88: J4.20, U4.21 (OUT16)
/LED_89: J4.19, U4.22 (OUT17)
/LED_90: J4.18, U4.23 (OUT18)
/LED_91: J4.17, U4.24 (OUT19)
/LED_92: J4.16, U4.25 (OUT20)
/LED_93: J4.15, U4.26 (OUT21)
/LED_94: J4.14, U4.27 (OUT22)
/LED_95: J4.13, U4.28 (OUT23)
/LED_BLANK: J1.7, R10.1, U5.6 (A4)
/LED_MOSI: J1.4, R19.1, U5.3 (A1)
/LED_SCK: J1.5, R20.1, U5.4 (A2)
/LED_XLAT: J1.6, R21.1, U5.5 (A3)
/OE_N: Q1.3 (D), R5.1, U5.22 (OE_N)
/PG_3V3: Q1.1 (G), R6.1, R8.1, U6.1 (RESET_N)
/PG_5V: Q2.1 (G), R7.1, R9.1, U7.1 (RESET_N)
/SERIAL_0: U1.29 (SOUT), U2.4 (SIN)
/SERIAL_1: U2.29 (SOUT), U3.4 (SIN)
/SERIAL_2: U3.29 (SOUT), U4.4 (SIN)
/V3V3_IO: C9.1, C11.1, J1.3, R5.2, R6.2, R10.2, U5.1 (VCCA), U5.2 (DIR), U6.3 (MR_N), U6.5 (SENSE), U6.6 (VDD)

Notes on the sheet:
E20 -96-channel constant-current LED/display driver. MCU->U1->U2->U3->U4; global n uses chip n/24 and OUT(n%24).
5V powers driver logic and common anodes; dual-supply translator isolates processor3.3V. Both rails must qualify before outputs enable.
Proposed91x27mm PCB at(197,77), seat6.5mm beneath scene controls; exact footprints/PCB/fit remain to be verified.
3mA is nominal, not a guaranteed low-current bound. E14/E17 digital power budget must include driver ICC. No fabrication or physical validation approval.
